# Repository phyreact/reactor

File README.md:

# Reactor

**A world that can be seen, heard, and sensed.**

Someone calls from across the room. A hand moves beside the camera. The surface
under a device shifts. Each moment carries a cue about what is happening nearby.

We want to build machines that can notice those cues and respond in ways people
understand. Reactor explores that idea through two devices: an expressive robot
and a compact sensing hub. They share a Radxa ZERO 3W host and four-microphone
audio, with different bodies and ways to interact.

## Meet the projects

| Donald Microduck | Mickey Hub |
| :--- | :--- |
|  |  |
| **Give listening a body.** A small robot with four microphones, a camera, a speaker and 15 smart servos. | **Bring perception together.** Four microphones, three radars, a camera, depth sensing, motion sensors and dual displays. |
| [**Explore Donald Microduck →**](donald-microduck/) | [**Explore Mickey Hub →**](mickeyhub/) |

Each project has its own guide, animated previews, STL parts, one final assembled
Blender model, firmware and build instructions. The GIFs above show the devices rotating, separating
into modules and coming back together, with English explanations.

## What you can explore

| Area | Donald Microduck | Mickey Hub |
| --- | --- | --- |
| Hearing | Four-microphone ReSpeaker hardware; current firmware provides 16 kHz stereo processed audio. | Four-microphone ReSpeaker hardware and a speaker for audio experiments. |
| Perception | Camera and motion sensing in a moving robot. | Ultra-wide camera, 8 × 8 ToF depth sensing, three radar modules, six-axis IMU and compass. |
| Interaction | Speaker, expressive pose and 15 smart servos. | Glasses-like dual displays, speaker, light ring, controls and additional I/O. |
| Design files | One final assembled Blender model and 37 printable STL parts. | One final assembled Blender model, 15 printable STL parts, four fit samples and native KiCad projects. |
| Development | [Firmware](donald-microduck/firmware/) · [Host tools](donald-microduck/software/) · [Simulation](donald-microduck/sim/) | [Firmware](mickeyhub/firmware/) · [Electronics](mickeyhub/electronics/) · [Simulation](mickeyhub/simulation/) |

These are evolving hardware projects. Sound-source localization, sensor fusion
and autonomous responses are development goals. Each project guide distinguishes
the supplied files and recorded checks from work that still needs assembled
hardware testing.

## Start exploring

1. **Choose a project above.** Its README introduces the device and points to the relevant files.
2. **Retrieve the large models with Git LFS.** Run these commands inside your checkout:

   ```sh
   git lfs install --local
   git lfs pull
   ```

3. **Open an editable assembly.** Start with
   [Donald Microduck](donald-microduck/mechanical/duck.blend) or
   [Mickey Hub](mickeyhub/mickeyhub.blend), then follow the project's build guide.

The repository includes firmware and application sources, native electronics,
manufacturing files, STL exports, one final assembled Blender file per project,
GIF previews and captions. Component GLBs, STEP references, intermediate design
files, separate animation scenes and full MP4 renders stay in the local
`memory_backups/` directory, alongside render caches and conversation history.
They are excluded from commits and source archives.

## Contribute

Work on mechanical fit, audio processing, perception, firmware, host applications
and interaction design is welcome. Identify the affected project, explain the
change and include the checks needed to reproduce your result.

## Licenses

| Project | Terms |
| --- | --- |
| **Donald Microduck** | Preserves the official upstream Apache-2.0 software license and the upstream noncommercial, share-alike model notice. [Upstream terms](donald-microduck/UPSTREAM_LICENSES.md). |
| **Mickey Hub** | First-party designs and content: **CC BY-NC 4.0**. First-party firmware and tools: **PolyForm Noncommercial 1.0.0**. Additional permission allows **up to 100 covered units sold per entity per calendar year** without a license fee. [License](mickeyhub/LICENSE). |

Mickey Hub's [limited commercial permission](mickeyhub/COMMERCIAL_USE.md)
covers up to and including 100 devices or one-device kits sold by the same
individual or legal entity each calendar year. Before selling the 101st unit,
obtain separate written authorization from the Reactor maintainers.
The complete grant defines the counting rules and third-party exclusions.

Original shared documentation and graphics use CC BY-NC 4.0.
Third-party material retains its own terms. [LICENSING.md](LICENSING.md)
defines the project scopes, commercial authorization and model exceptions;
[THIRD_PARTY.md](THIRD_PARTY.md) records upstream sources.

---

<sub>For questions or commercial licensing, contact [phyreact@gmail.com](mailto:phyreact@gmail.com).</sub>

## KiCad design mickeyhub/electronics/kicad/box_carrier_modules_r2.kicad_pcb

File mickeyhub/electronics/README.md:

# Schematic, PCB and libraries

## Board previews

Front and back bare-board views come directly from
[the native carrier PCB](kicad/box_carrier_modules_r2.kicad_pcb), rendered in
KiCad. Click any preview to inspect the large image.

This populated view uses the mounted electronics from the final
[integrated Blender assembly](../mickeyhub.blend). Components retain their
source geometry, materials and placement; the enclosure and remote devices are
hidden. Purchased-module models include simplified reference geometry.

For the system-level relationships, see the
[hardware functional overview](../docs/HARDWARE_OVERVIEW.md).

## Editable sources and board identity

Open [kicad/box_carrier_modules_r2.kicad_pro](kicad/box_carrier_modules_r2.kicad_pro) in KiCad. The project retains its original electrical identifier, BOX R2.1R. The product is mickeyhub.

`kicad/` includes schematic sheets, the PCB, project settings, local symbols,
footprints and datasheets. The carrier has a monochrome icon traced from the
actual enclosure and the marking **MicheyHub V0.0**. The editable
[SVG icon](branding/mickeyhub-mark.svg) and native KiCad polygons are both included.

The preview is cropped from the native silkscreen export and rotated for reading.

[branding.json](branding.json) records the changed graphics and source hashes.
All other raw KiCad blocks match the archived source, including copper, nets,
pads, footprints, board outline and settings.
[library_relocation.json](library_relocation.json) records the earlier
project-relative JST 3D-model path change. STEP and VRML reference models are
now archived locally; their optional preview paths remain in the unchanged
PCB and footprint files. The release verifier checks board integrity and
manufacturing outputs without requiring those archived 3D previews.

[schematic.pdf](schematic.pdf) is the existing schematic publication. [bom/mickeyhub-board-bom.csv](bom/mickeyhub-board-bom.csv) was exported recursively from the included schematic. It is an engineering BOM, not a current stock/price or assembly-order quotation. Component/module selections and reference evidence are in [../components](../components/).

Native KiCad checks on the relocated copy are in `validation/`: DRC 0, ERC 0, unconnected items 0, schematic parity issues 0. These results address CAD rules and consistency, not unresolved system power and module compatibility. Read [../docs/CURRENT_STATUS.md](../docs/CURRENT_STATUS.md) before using the connection proposals.

Local footprint libraries retain the entries referenced by the delivered
schematics, PCBs, symbols and adapter records. Unused variants and intermediate
netlist/analysis exports are archived. `kicad/datasheets/` is the canonical
location for project datasheets, shared by the component documentation.

`daughterboards/` contains the editable RP and S3 adapter projects, each with its
own local symbol library. The adapters carry the same product/version marking.
Their native DRC and ERC results are recorded in
[validation/adapters.json](validation/adapters.json). Inspect the complete device
in [mickeyhub.blend](../mickeyhub.blend) and use the
[component catalog](../components/) for module descriptions.

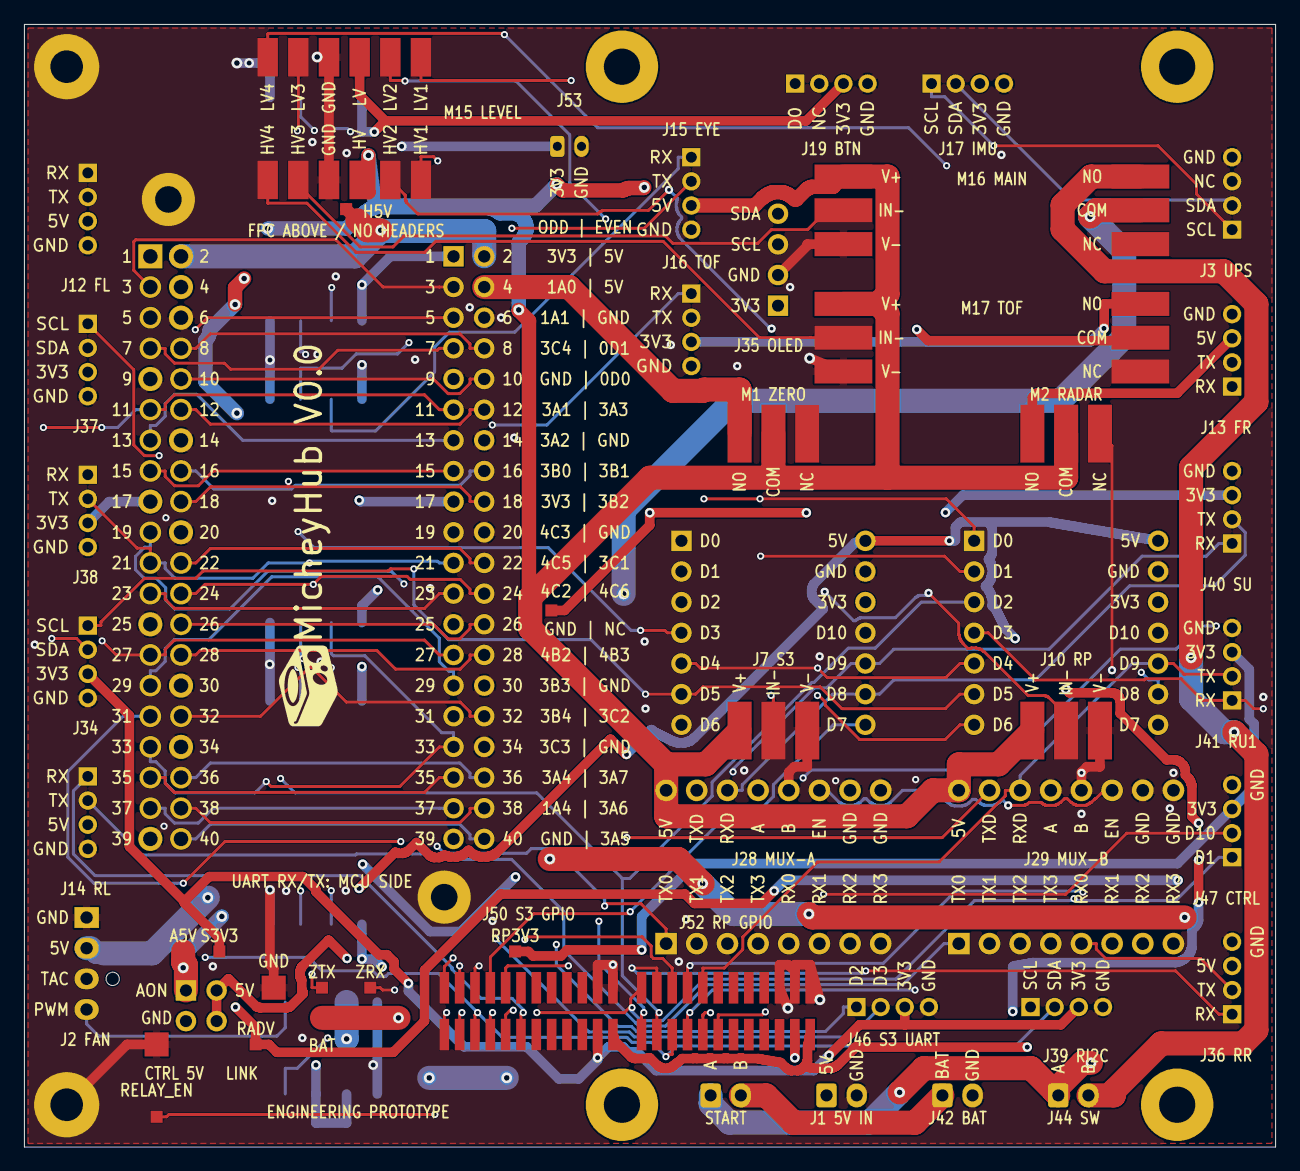
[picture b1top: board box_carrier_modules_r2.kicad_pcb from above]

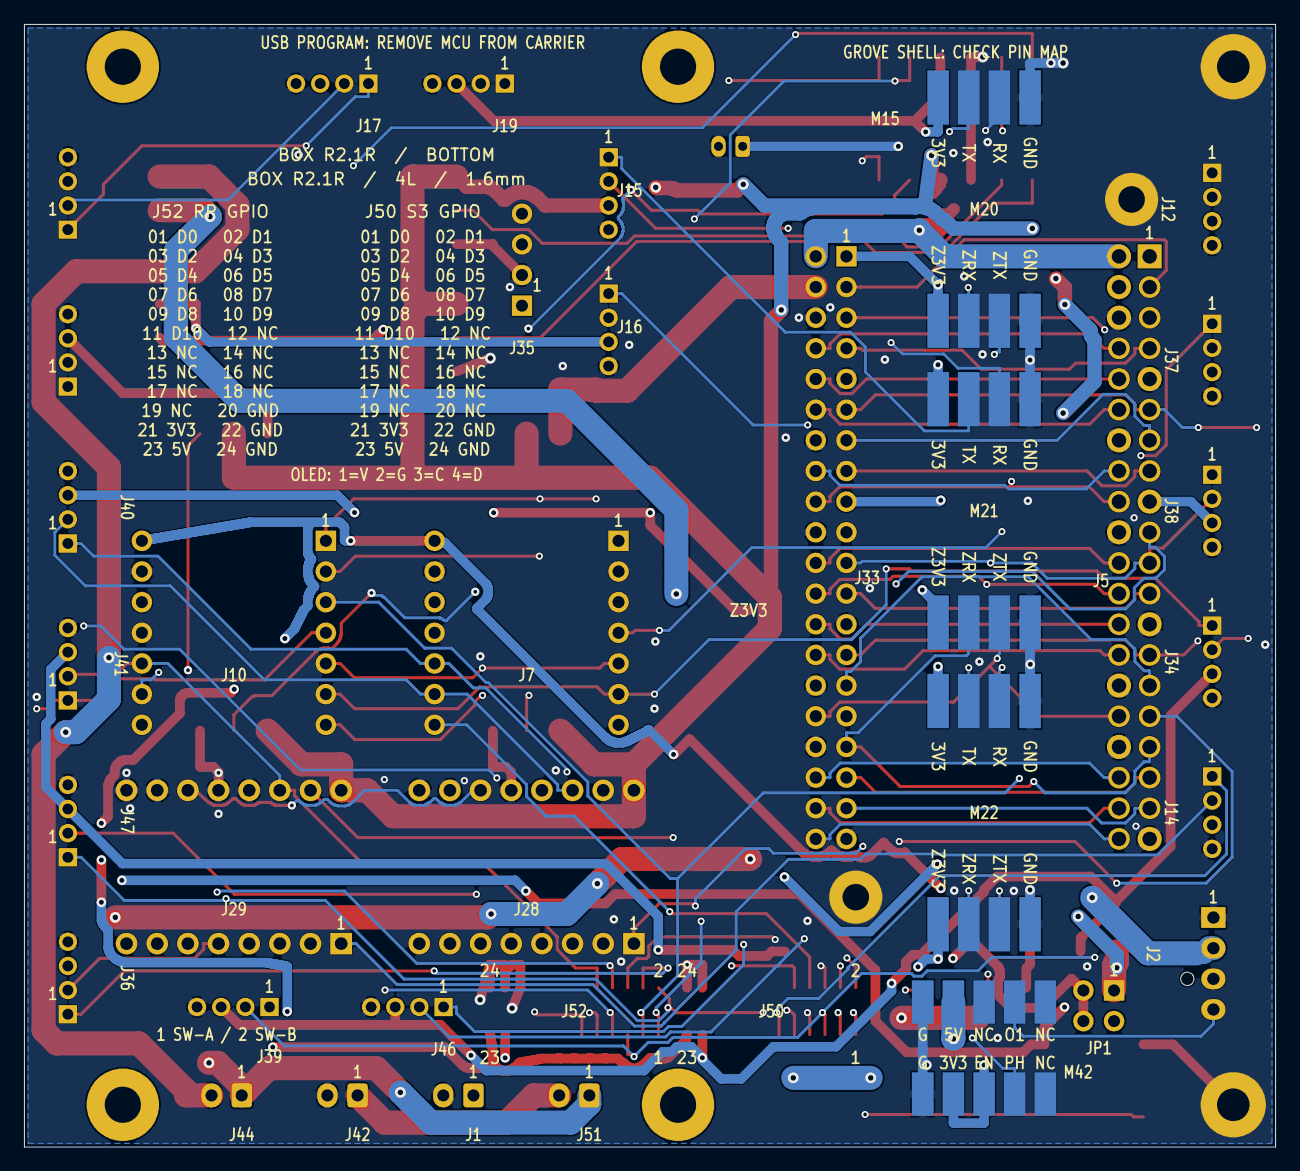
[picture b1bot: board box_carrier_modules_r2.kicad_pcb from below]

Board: 4 copper layers, 103.7 x 93.0 mm, 61 parts (5 on the bottom side), 74 nets.

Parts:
H1, H3: MountingHole_2.7mm_M2.5_Pad
J1: UPS REGULATED 5V; JST_XH_B2B-XH-A_1x02_P2.50mm_Vertical
J2: ZERO FAN / NOCTUA 5V PWM / 4P; FanPinHeader_1x04_P2.54mm_Vertical
J3: UPS I2C STATUS; NS-Tech_Grove_1x04_P2mm_Vertical_J3_SilkClearance
J5: Radxa ZERO 3W SOCKET; Zero_socket40_PROVISIONAL
J7: S3 / Seeed XIAO SOCKET14; Seeed_XIAO_14pin_Socket
J10: RP / Seeed XIAO SOCKET14; Seeed_XIAO_14pin_Socket
J12: LD2450 / FRONT LEFT; NS-Tech_Grove_1x04_P2mm_Vertical
J13: LD2450 / FRONT RIGHT; NS-Tech_Grove_1x04_P2mm_Vertical
J14: LD2450 / REAR LEFT; NS-Tech_Grove_1x04_P2mm_Vertical
J15: EYES; NS-Tech_Grove_1x04_P2mm_Vertical
J16: SEN0628 / UART4; NS-Tech_Grove_1x04_P2mm_Vertical
J17: IMU; NS-Tech_Grove_1x04_P2mm_Vertical
J19: FRONT BUTTON; NS-Tech_Grove_1x04_P2mm_Vertical
J28: MUX / FRONT PAIR TX GATE; UART_MUX_SOCKET_16_USER_PINOUT
J29: MUX / REAR PAIR TX GATE; UART_MUX_SOCKET_16_USER_PINOUT
J33: ZERO GPIO COPY / FULL40 1:1; HAT_P4_M20_9982046_2x20
J34: S3 I2C; NS-Tech_Grove_1x04_P2mm_Vertical
J35: OLED / PARALLEL / SCREEN UP; SSW_104_01_G_S_OLED_Parallel
J36: LD2450 / REAR RIGHT; NS-Tech_Grove_1x04_P2mm_Vertical
J37: ZERO I2C4; NS-Tech_Grove_1x04_P2mm_Vertical
J38: ZERO RP UART9; NS-Tech_Grove_1x04_P2mm_Vertical
J39: RP I2C SHARED; NS-Tech_Grove_1x04_P2mm_Vertical
J40: S3 UART A; NS-Tech_Grove_1x04_P2mm_Vertical
J41: RP UART1; NS-Tech_Grove_1x04_P2mm_Vertical
J42: UPS BAT OUT; JST_XH_B2B-XH-A_1x02_P2.50mm_Vertical
J44: UPS SWITCH LOOP; JST_XH_B2B-XH-A_1x02_P2.50mm_Vertical
J46: S3 D2 D3 / FRONT LEFT UART; NS-Tech_Grove_1x04_P2mm_Vertical
J47: RP D1 / ZERO RELAY; NS-Tech_Grove_1x04_P2mm_Vertical
J50: S3 EDGE GPIO D0-D10 / AUX NC; Harwin_M50-3601242_2x12_P1.27_SMT_CENTERED
J51: PANEL START / MOMENTARY NO; JST_XH_B2B-XH-A_1x02_P2.50mm_Vertical
J52: RP EDGE GPIO D0-D10 / AUX NC; Harwin_M50-3601242_2x12_P1.27_SMT_CENTERED
J53: EYES 3V3 REFERENCE INPUT; JST_PH_B2B-PH-K_1x02_P2.00mm_Vertical
JP1: COMMON CTRL 5V LINK / TWO SHUNTS; Dual_Power_Shunt_2x02
M1: M1 / 5V RELAY / ZERO + HAT; ZXC0073_28p08x8p55_FLUSH_SMD_PENDING
M2: M2 / 5V RELAY / FOUR LD2450; ZXC0073_28p08x8p55_FLUSH_SMD_PENDING
M15: SPARKFUN BOB-12009 / 4CH BSS138; SparkFun_BOB12009_Module_SolderLands
M16: M16 / MAIN HOLD / LOAD QUALIFY; ZXC0073_28p08x8p55_FLUSH_SMD_PENDING
M17: M17 / 5V RELAY / SEN0628 TOF; ZXC0073_28p08x8p55_FLUSH_SMD_PENDING
M20: ZERO RP UART9 / ADUM1201; LA161062_ADuM1201_REAR_LANDS
M21: ZERO EYES UART5 / ADUM1201; LA161062_ADuM1201_REAR_LANDS
M22: ZERO TOF UART4 / ADUM1201; LA161062_ADuM1201_REAR_LANDS
M42: FAN PWM / POLOLU 2990; Pololu_2990_REAR_LANDS
MH_UPS1, MH_UPS2, MH_UPS3, MH_UPS4: UPS M2.5 / 3mm PTH / isolated 6.0mm copper; UPS_M2p5_PTH_3mm_Copper6p0_Isolated
MH_ZERO: ZERO socket support / UNQUALIFIED
TP1, TP10: GND; COPPER_TEST_2MM
TP2: A5V; COPPER_TEST_1MM
TP3: H5V; COPPER_TEST_1MM
TP4: Z3V3; COPPER_TEST_1MM
TP5: RP3V3; COPPER_TEST_1MM
TP6: S3V3; COPPER_TEST_1MM
TP7: ZTX; COPPER_TEST_1MM
TP8: ZRX; COPPER_TEST_1MM
TP9: RELAY_EN; COPPER_TEST_1MM
TP11: RADV; COPPER_TEST_1MM
TP13: BAT; COPPER_TEST_1MM

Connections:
+3V3_EYES: J53.1, M21.5
+3V3_RP: J10.12, J19.3, J41.3, J47.3, J52.21, M15.LV, M20.5, TP5.1
+3V3_S3: J7.12, J17.3, J34.3, J35.1, J39.3, J40.3, J46.3, J50.21, TP6.1
+3V3_TOF_SW: J16.3, M17.NO, M22.5
+3V3_ZERO: J5.1, J5.17, J33.1, J33.17, J37.3, J38.3, M17.COM, M20.1, M21.1, M22.1, M42.ENABLE, M42.VCC, TP4.1
+5V_AON: J1.1, J15.3, J28.2, J29.2, JP1.1, JP1.3, M1.COM, M1.V+, M2.COM, M2.V+, M15.HV, M16.V+, M17.V+, TP2.1
+5V_HOST: J2.2, J5.2, J5.4, J33.2, J33.4, M1.NO, M42.VIN, TP3.1
+5V_LOGIC: J7.14, J10.14, J50.23, J52.23, JP1.2, JP1.4
+UPS_SW_A: J44.1, J51.1, M16.COM
+VBAT_UPS_SW: J42.1, J44.2, J51.2, M16.NO, TP13.1
+V_RADAR_SW: J12.3, J13.3, J14.3, J36.3, M2.NO, TP11.1
EYES_RX: J15.2, M21.7
EYES_TX: J15.1, M21.6
FAN_PWM_5V: J2.4, M42.OUT1
GND: H1.1, H3.1, J1.2, J2.1, J3.4, J5.6, J5.9, J5.14, J5.20, J5.25, J5.30, J5.34, J5.39, J7.13, J10.13, J12.4, J13.4, J14.4, J15.4, J16.4, J17.4, J19.4, J28.8, J28.10, J28.14, J28.16, J29.8, J29.10, J29.14, J29.16, J33.6, J33.9, J33.14, J33.20, J33.25, J33.30, J33.34, J33.39, J34.4, J35.2, J36.4, J37.4, J38.4, J39.4, J40.4, J41.4, J42.2, J46.4, J47.4, J50.22, J50.24, J52.20, J52.22, J52.24, J53.2, M1.V-, M2.V-, M15.GND_H, M15.GND_L, M16.V-, M17.V-, M20.4, M20.8, M21.4, M21.8, M22.4, M22.8, M42.GND1, M42.GND2, MH_ZERO.1, MH_ZERO.2, TP1.1, TP10.1
MAIN_HOLD_IN_N: M15.HV3, M16.IN-
RADAR_FL_RX: J12.2, J28.1
RADAR_FR_RX: J13.2, J28.9
RADAR_MUX_INHIBIT: J28.12 (EN), J29.12 (EN), M2.NC (MUX INHIBIT WHEN OFF)
RADAR_RELAY_IN_N: M2.IN-, M15.HV2
RADAR_RL_RX: J14.2, J29.1
RADAR_RR_RX: J29.9, J36.2
RP_D0: J10.1, J19.1, J52.1
RP_D1: J10.2, J47.1, J52.2, M15.LV1, TP9.1
RP_D2: J10.3, J52.3, M15.LV3
RP_D3: J10.4, J36.1, J41.1, J52.4
RP_D8: J10.9, J52.9, M15.LV4
RP_D9: J10.10, J29.6, J41.2, J52.10
RP_D10: J10.11, J47.2, J52.11
RP_UART0_RX: J10.8, J52.8, M20.7
RP_UART0_TX: J10.7, J52.7, M20.6
S3_D0: J7.1, J29.4, J50.1
S3_D1: J7.2, J50.2, M15.LV2
S3_D2: J7.3, J28.4, J46.1, J50.3
S3_D3: J7.4, J12.1, J46.2, J50.4
S3_D4: J3.2, J7.5, J10.5, J17.2, J34.2, J35.4, J39.2, J50.5, J52.5
S3_D5: J3.1, J7.6, J10.6, J17.1, J34.1, J35.3, J39.1, J50.6, J52.6
S3_D6: J7.7, J50.7
S3_D7: J7.8, J50.8
S3_D8: J7.9, J28.6, J40.2, J50.9
S3_D9: J7.10, J13.1, J40.1, J50.10
S3_D10: J7.11, J14.1, J50.11
TOF_RELAY_IN_N: M15.HV4, M17.IN-
TOF_RX: J16.2, M22.7
TOF_TX: J16.1, M22.6
ZERO_RELAY_IN_N: M1.IN-, M15.HV1
Z_GPIO0_D0: J5.10, J33.10, TP8.1
Z_GPIO0_D1: J5.8, J33.8, TP7.1
Z_GPIO1_A0: J5.3, J33.3
Z_GPIO1_A1: J5.5, J33.5
Z_GPIO1_A4: J5.37, J33.37
Z_GPIO3_A1: J2.3, J5.11, J33.11
Z_GPIO3_A2: J5.13, J33.13
Z_GPIO3_A3: J5.12, J33.12
Z_GPIO3_A4: J5.35, J33.35
Z_GPIO3_A5: J5.40, J33.40
Z_GPIO3_A6: J5.38, J33.38
Z_GPIO3_A7: J5.36, J33.36
Z_GPIO3_B0: J5.15, J33.15
Z_GPIO3_B1: J5.16, J33.16, M22.2
Z_GPIO3_B2: J5.18, J33.18, M22.3
Z_GPIO3_B3: J5.29, J33.29
Z_GPIO3_B4: J5.31, J33.31
Z_GPIO3_C1: J5.22, J33.22
Z_GPIO3_C2: J5.32, J33.32, M21.3
Z_GPIO3_C3: J5.33, J33.33, M21.2
Z_GPIO3_C4: J5.7, J33.7, M42.PHASE
Z_GPIO4_B2: J5.27, J33.27, J37.2
Z_GPIO4_B3: J5.28, J33.28, J37.1
Z_GPIO4_C2: J5.23, J33.23
Z_GPIO4_C3: J5.19, J33.19
Z_GPIO4_C5: J5.21, J33.21, J38.2, M20.3
Z_GPIO4_C6: J5.24, J33.24, J38.1, M20.2
Z_PHYSICAL26_NC_COPY: J5.26, J33.26

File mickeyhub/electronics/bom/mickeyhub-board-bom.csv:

Reference,Qty,Value,Footprint,MPN,Manufacturer,Chosen_Distributor,Datasheet,Validated,DNP,Notes
J1,1,UPS REGULATED 5V,JST_XH_B2B-XH-A_1x02_P2.50mm_Vertical,B2B-XH-A(LF)(SN),JST,,https://www.jst-mfg.com/product/pdf/eng/eXH.pdf,,,
J2,1,ZERO FAN / NOCTUA 5V PWM / 4P,FanPinHeader_1x04_P2.54mm_Vertical,47053-1000,Molex,,https://cdn.noctua.at/media/Noctua_PWM_specifications_white_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,,,
J3,1,UPS I2C STATUS,NS-Tech_Grove_1x04_P2mm_Vertical_J3_SilkClearance,1125S-4P,Shenzhen NS-Tech,,https://statics3.seeedstudio.com/images/opl/datasheet/3470130P1.pdf,,,
J5,1,Radxa ZERO 3W SOCKET,Zero_socket40_PROVISIONAL,,,,,,,
J7,1,S3 / Seeed XIAO SOCKET14,Seeed_XIAO_14pin_Socket,,Seeed Studio,,,,,
J10,1,RP / Seeed XIAO SOCKET14,Seeed_XIAO_14pin_Socket,,Seeed Studio,,,,,
J12,1,LD2450 / FRONT LEFT,NS-Tech_Grove_1x04_P2mm_Vertical,1125S-4P,Shenzhen NS-Tech,,https://statics3.seeedstudio.com/images/opl/datasheet/3470130P1.pdf,,,
J13,1,LD2450 / FRONT RIGHT,NS-Tech_Grove_1x04_P2mm_Vertical,1125S-4P,Shenzhen NS-Tech,,https://statics3.seeedstudio.com/images/opl/datasheet/3470130P1.pdf,,,
J14,1,LD2450 / REAR LEFT,NS-Tech_Grove_1x04_P2mm_Vertical,1125S-4P,Shenzhen NS-Tech,,https://statics3.seeedstudio.com/images/opl/datasheet/3470130P1.pdf,,,
J15,1,EYES,NS-Tech_Grove_1x04_P2mm_Vertical,1125S-4P,Shenzhen NS-Tech,,https://statics3.seeedstudio.com/images/opl/datasheet/3470130P1.pdf,,,
J16,1,SEN0628 / UART4,NS-Tech_Grove_1x04_P2mm_Vertical,1125S-4P,Shenzhen NS-Tech,,https://statics3.seeedstudio.com/images/opl/datasheet/3470130P1.pdf,,,
J17,1,IMU,NS-Tech_Grove_1x04_P2mm_Vertical,1125S-4P,Shenzhen NS-Tech,,https://statics3.seeedstudio.com/images/opl/datasheet/3470130P1.pdf,,,
J19,1,FRONT BUTTON,NS-Tech_Grove_1x04_P2mm_Vertical,1125S-4P,Shenzhen NS-Tech,,https://statics3.seeedstudio.com/images/opl/datasheet/3470130P1.pdf,,,
J28,1,MUX / FRONT PAIR TX GATE,UART_MUX_SOCKET_16_USER_PINOUT,Taobao-1011201977739,User-selected TTL multiplexer module,,,,,
J29,1,MUX / REAR PAIR TX GATE,UART_MUX_SOCKET_16_USER_PINOUT,Taobao-1011201977739,User-selected TTL multiplexer module,,,,,
J33,1,ZERO GPIO COPY / FULL40 1:1,HAT_P4_M20_9982046_2x20,M20-9982046,Harwin,,https://content.harwin.com/asset/1590d228-db5c-4836-ab0c-0f1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,,,
J34,1,S3 I2C,NS-Tech_Grove_1x04_P2mm_Vertical,1125S-4P,Shenzhen NS-Tech,,https://statics3.seeedstudio.com/images/opl/datasheet/3470130P1.pdf,,,
J35,1,OLED / PARALLEL / SCREEN UP,SSW_104_01_G_S_OLED_Parallel,SSW-104-01-G-S,Samtec,,https://suddendocs.samtec.com/prints/ssw-1xx-xx-xxx-x-xx-xxx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,,,
J36,1,LD2450 / REAR RIGHT,NS-Tech_Grove_1x04_P2mm_Vertical,1125S-4P,Shenzhen NS-Tech,,https://statics3.seeedstudio.com/images/opl/datasheet/3470130P1.pdf,,,
J37,1,ZERO I2C4,NS-Tech_Grove_1x04_P2mm_Vertical,1125S-4P,Shenzhen NS-Tech,,https://statics3.seeedstudio.com/images/opl/datasheet/3470130P1.pdf,,,
J38,1,ZERO RP UART9,NS-Tech_Grove_1x04_P2mm_Vertical,1125S-4P,Shenzhen NS-Tech,,https://statics3.seeedstudio.com/images/opl/datasheet/3470130P1.pdf,,,
J39,1,RP I2C SHARED,NS-Tech_Grove_1x04_P2mm_Vertical,1125S-4P,Shenzhen NS-Tech,,https://statics3.seeedstudio.com/images/opl/datasheet/3470130P1.pdf,,,
J40,1,S3 UART A,NS-Tech_Grove_1x04_P2mm_Vertical,1125S-4P,Shenzhen NS-Tech,,https://statics3.seeedstudio.com/images/opl/datasheet/3470130P1.pdf,,,
J41,1,RP UART1,NS-Tech_Grove_1x04_P2mm_Vertical,1125S-4P,Shenzhen NS-Tech,,https://statics3.seeedstudio.com/images/opl/datasheet/3470130P1.pdf,,,
J42,1,UPS BAT OUT,JST_XH_B2B-XH-A_1x02_P2.50mm_Vertical,B2B-XH-A(LF)(SN),JST,,https://www.jst-mfg.com/product/pdf/eng/eXH.pdf,,,
J44,1,UPS SWITCH LOOP,JST_XH_B2B-XH-A_1x02_P2.50mm_Vertical,B2B-XH-A(LF)(SN),JST,,https://www.jst-mfg.com/product/pdf/eng/eXH.pdf,,,
J45,1,EXTERNAL DC DIRECT TO UPS,,,,,,,,
J46,1,S3 D2 D3 / FRONT LEFT UART,NS-Tech_Grove_1x04_P2mm_Vertical,1125S-4P,Shenzhen NS-Tech,,https://statics3.seeedstudio.com/images/opl/datasheet/3470130P1.pdf,,,
J47,1,RP D1 / ZERO RELAY,NS-Tech_Grove_1x04_P2mm_Vertical,1125S-4P,Shenzhen NS-Tech,,https://statics3.seeedstudio.com/images/opl/datasheet/3470130P1.pdf,,,
J50,1,S3 EDGE GPIO D0-D10 / AUX NC,Harwin_M50-3601242_2x12_P1.27_SMT_CENTERED,M50-3601242,Harwin,,https://www.harwin.com/products/M50-3601242,,,
J51,1,PANEL START / MOMENTARY NO,JST_XH_B2B-XH-A_1x02_P2.50mm_Vertical,B2B-XH-A(LF)(SN),JST,,https://www.jst-mfg.com/product/pdf/eng/eXH.pdf,,,
J52,1,RP EDGE GPIO D0-D10 / AUX NC,Harwin_M50-3601242_2x12_P1.27_SMT_CENTERED,M50-3601242,Harwin,,https://www.harwin.com/products/M50-3601242,,,
J53,1,EYES 3V3 REFERENCE INPUT,JST_PH_B2B-PH-K_1x02_P2.00mm_Vertical,B2B-PH-K-S,JST,,https://www.jst-mfg.com/product/pdf/eng/ePH.pdf,,,
JP1,1,COMMON CTRL 5V LINK / TWO SHUNTS,Dual_Power_Shunt_2x02,,,,,,,
M1,1,M1 / 5V RELAY / ZERO + HAT,ZXC0073_28p08x8p55_FLUSH_SMD_PENDING,,,,,,,
M2,1,M2 / 5V RELAY / FOUR LD2450,ZXC0073_28p08x8p55_FLUSH_SMD_PENDING,,,,,,,
M3,1,EXISTING 0.96in SSD1306 OLED / I2C,External_Module_Not_On_Carrier,15628-0.96,DORHEA,,,,,
M4,1,NOCTUA NF-A4x10 5V PWM / FOUR-WIRE,External_Module_Not_On_Carrier,NF-A4x10 5V PWM,Noctua,,https://www.noctua.at/en/products/nf-a4x10-5v-pwm,,,
M5,1,COMPLETE Waveshare Servo Driver HAT (B),External_Module_Not_On_Carrier,17035,Waveshare,,https://files.waveshare.com/upload/a/a2/Servo_Driver_HAT_Sch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,,,
M6,1,REMOTE HLK-LD2450 / FRONT LEFT,External_Module_Not_On_Carrier,HLK-LD2450,Hi-Link,,https://www.hlktech.com/Goods-352.html,,,
M7,1,REMOTE HLK-LD2450 / FRONT RIGHT,External_Module_Not_On_Carrier,HLK-LD2450,Hi-Link,,https://www.hlktech.com/Goods-352.html,,,
M8,1,REMOTE HLK-LD2450 / REAR LEFT,External_Module_Not_On_Carrier,HLK-LD2450,Hi-Link,,https://www.hlktech.com/Goods-352.html,,,
M9,1,DFRobot SEN0628 / UART 115200,External_Module_Not_On_Carrier,SEN0628,DFRobot,,https://wiki.dfrobot.com/sen0628/,,,
M10,1,COMPLETE Waveshare UPS Module 3S,External_Module_Not_On_Carrier,UPS Module 3S / 23884,Waveshare,,https://www.waveshare.com/wiki/UPS_Module_3S,,,
M11,1,EXISTING ReSpeaker XIAO USB endpoint,External_Module_Not_On_Carrier,,,,,,,
M12,1,EXISTING ZERO USB HOST endpoint,External_Module_Not_On_Carrier,,,,,,,
M13,1,EXISTING WAVESHARE DUAL EYES / LCD1 P2,External_Module_Not_On_Carrier,ESP32-S3-DualEye-Touch-LCD-1.28,Waveshare,,https://www.waveshare.com/wiki/ESP32-S3-DualEye-Touch-LCD-1.28,,,
M14,1,EXISTING GROVE LSM6DS3 / J4,External_Module_Not_On_Carrier,,Seeed Studio,,https://wiki.seeedstudio.com/Grove-6-Axis_AccelerometerAndGy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,,,
M15,1,SPARKFUN BOB-12009 / 4CH BSS138,SparkFun_BOB12009_Module_SolderLands,BOB-12009,SparkFun,,https://github.com/sparkfun/Logic_Level_Bidirectional,,,
M16,1,M16 / MAIN HOLD / LOAD QUALIFY,ZXC0073_28p08x8p55_FLUSH_SMD_PENDING,,,,,,,
M17,1,M17 / 5V RELAY / SEN0628 TOF,ZXC0073_28p08x8p55_FLUSH_SMD_PENDING,,,,,,,
M19,1,REMOTE HLK-LD2450 / REAR RIGHT,External_Module_Not_On_Carrier,HLK-LD2450,Hi-Link,,https://www.hlktech.com/Goods-352.html,,,
M20,1,ZERO RP UART9 / ADUM1201,LA161062_ADuM1201_REAR_LANDS,LA161062,LaskaKit,,https://www.laskakit.cz/en/digitalni-izolator-adum1201-2kana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,,,
M21,1,ZERO EYES UART5 / ADUM1201,LA161062_ADuM1201_REAR_LANDS,LA161062,LaskaKit,,https://www.laskakit.cz/en/digitalni-izolator-adum1201-2kana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,,,
M22,1,ZERO TOF UART4 / ADUM1201,LA161062_ADuM1201_REAR_LANDS,LA161062,LaskaKit,,https://www.laskakit.cz/en/digitalni-izolator-adum1201-2kana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,,,
M42,1,FAN PWM / POLOLU 2990,Pololu_2990_REAR_LANDS,2990,Pololu,,https://www.pololu.com/product/2990,,,
SW1,1,22mm MOMENTARY NO / PANEL START,External_Module_Not_On_Carrier,,22mm snap-in momentary NO panel switch; exact manufacturer/MPN pending,,,,,
